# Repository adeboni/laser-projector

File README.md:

# Room-scale Quad Laser Projecter

This project is for a quadruple laser projection controller, aimed at supporting room-scale projections

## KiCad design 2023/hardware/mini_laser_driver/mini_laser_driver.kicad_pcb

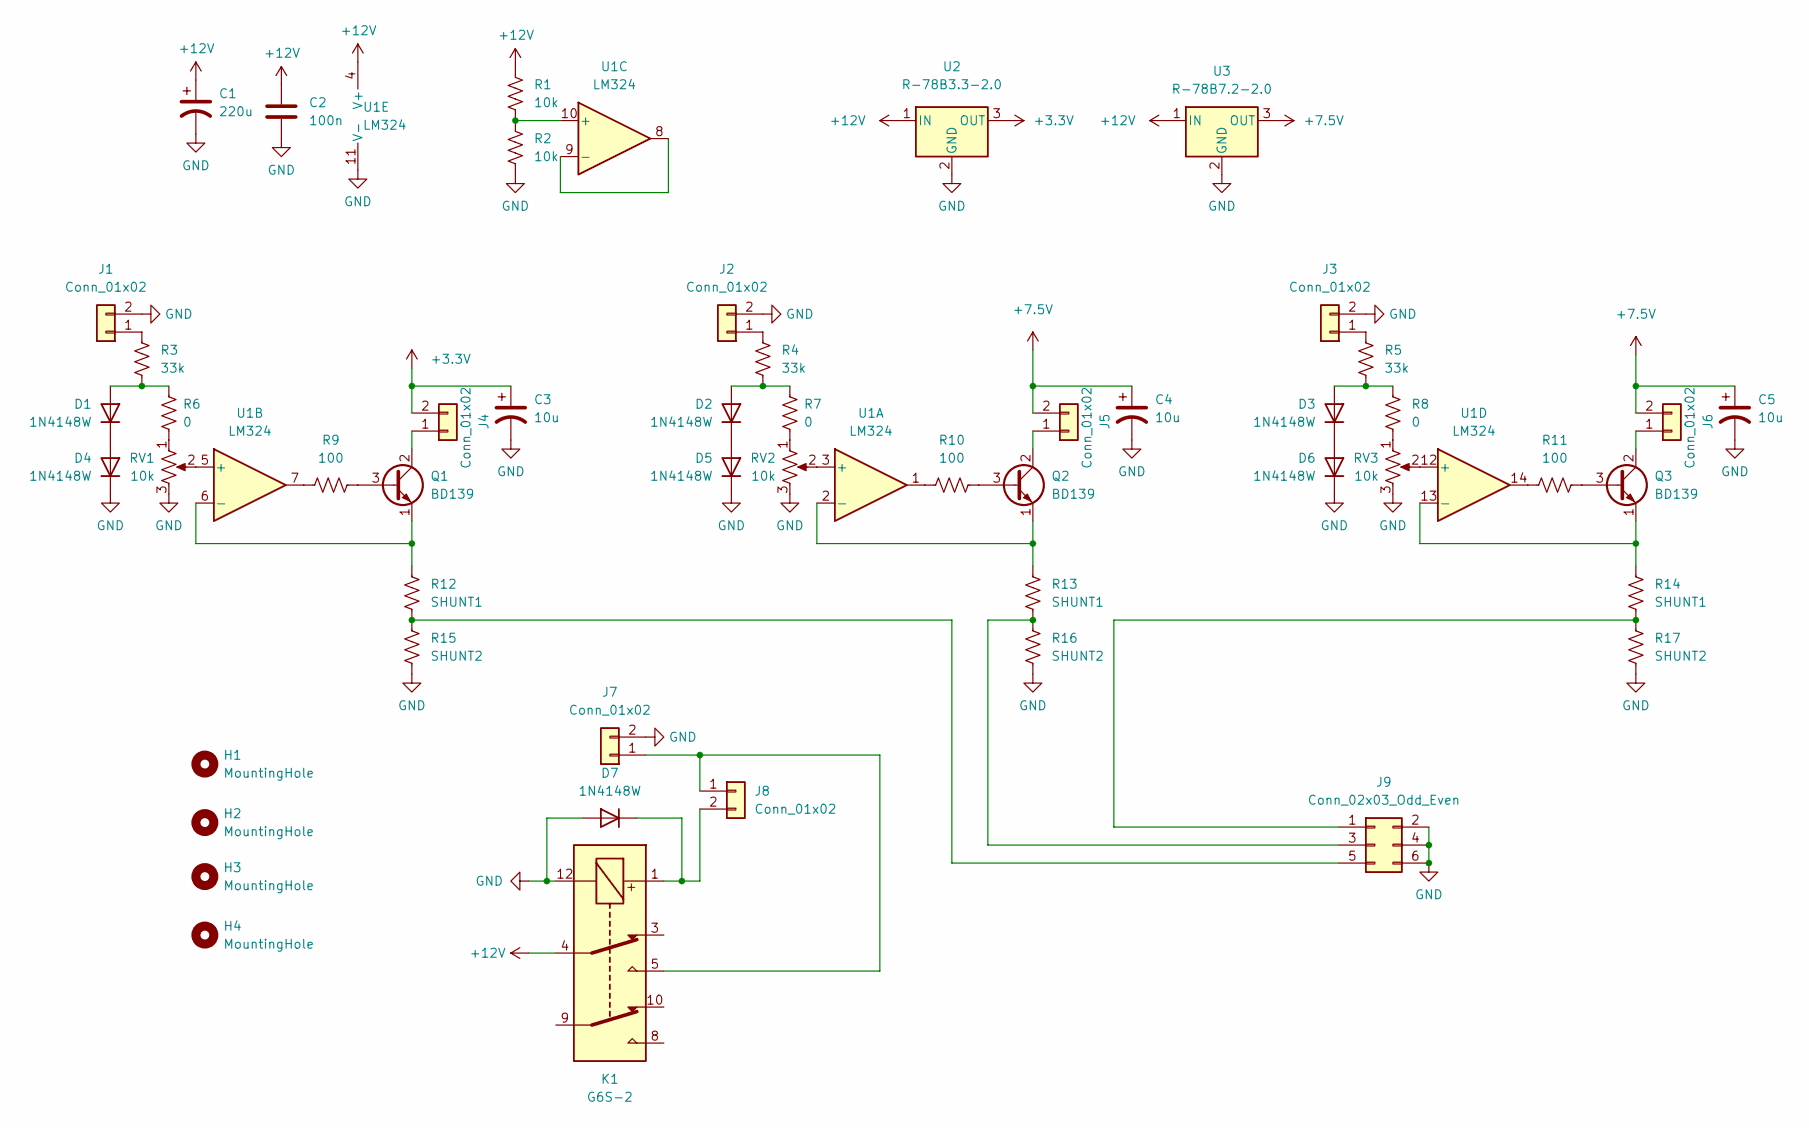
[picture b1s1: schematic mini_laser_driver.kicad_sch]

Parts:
C1: 220u; CP_Radial_D10.0mm_P5.00mm
C2: 100n; C_0603_1608Metric
C3, C4, C5: 10u; CP_Radial_D5.0mm_P2.50mm
D1, D2, D3, D4, D5, D6, D7: 1N4148W; D_SOD-123
H1, H2, H3, H4: MountingHole; MountingHole_3.2mm_M3
J1, J2, J3, J4, J5, J6, J7: Conn_01x02; JST_XH_B2B-XH-A_1x02_P2.50mm_Vertical
J8: Conn_01x02; PinHeader_1x02_P2.54mm_Vertical
J9: Conn_02x03_Odd_Even; PinHeader_2x03_P2.54mm_Vertical
K1: G6S-2; Relay_DPDT_Omron_G6S-2
Q1, Q2, Q3: BD139; TO-126-3_Vertical
R1, R2: 10k; R_0603_1608Metric
R3, R4, R5: 33k; R_0603_1608Metric
R6, R7, R8: 0; R_0603_1608Metric
R9, R10, R11: 100; R_0603_1608Metric
R12, R13, R14: SHUNT1; R_Axial_DIN0204_L3.6mm_D1.6mm_P1.90mm_Vertical
R15, R16, R17: SHUNT2; R_Axial_DIN0204_L3.6mm_D1.6mm_P1.90mm_Vertical
RV1, RV2, RV3: 10k; Potentiometer_Bourns_3296W_Vertical
U1: LM324; SOIC-14_3.9x8.7mm_P1.27mm
U2: R-78B3.3-2.0; Converter_DCDC_RECOM_R-78B-2.0_THT
U3: R-78B7.2-2.0; Converter_DCDC_RECOM_R-78B-2.0_THT

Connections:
+3V3: C3.1, J4.2, U2.3 (OUT)
+7.5V: C4.1, C5.1, J5.2, J6.2, U3.3 (OUT)
+12V: C1.1, C2.1, K1.4, R1.2, U1.4 (V+), U2.1 (IN), U3.1 (IN)
GND: C1.2, C2.2, C3.2, C4.2, C5.2, D4.1 (K), D5.1 (K), D6.1 (K), D7.2 (A), J1.2, J2.2, J3.2, J7.2, J9.2, J9.4, J9.6, K1.12, R2.1, R15.2, R16.2, R17.2, RV1.3, RV2.3, RV3.3, U1.11 (V-), U2.2 (GND), U3.2 (GND)
unnamed: D1.1 (K), D4.2 (A)
unnamed: D1.2 (A), R3.1, R6.2
unnamed: D2.1 (K), D5.2 (A)
unnamed: D2.2 (A), R4.1, R7.2
unnamed: D3.1 (K), D6.2 (A)
unnamed: D3.2 (A), R5.1, R8.2
unnamed: D7.1 (K), J8.2, K1.1
unnamed: J1.1, R3.2
unnamed: J2.1, R4.2
unnamed: J3.1, R5.2
unnamed: J4.1, Q1.2 (C)
unnamed: J5.1, Q2.2 (C)
unnamed: J6.1, Q3.2 (C)
unnamed: J7.1, J8.1, K1.5
unnamed: J9.1, R14.2, R17.1
unnamed: J9.3, R13.2, R16.1
unnamed: Q1.1 (E), R12.1, U1.6 (-)
unnamed: Q1.3 (B), R9.2
unnamed: Q2.1 (E), R13.1, U1.2 (-)
unnamed: Q2.3 (B), R10.2
unnamed: Q3.1 (E), R14.1, U1.13 (-)
unnamed: Q3.3 (B), R11.2
unnamed: R1.1, R2.2, U1.10 (+)
unnamed: R6.1, RV1.1
unnamed: R7.1, RV2.1
unnamed: R8.1, RV3.1
unnamed: R9.1, U1.7
unnamed: R10.1, U1.1
unnamed: R11.1, U1.14
unnamed: J9.5, R12.2, R15.1
unnamed: RV1.2, U1.5 (+)
unnamed: RV2.2, U1.3 (+)
unnamed: RV3.2, U1.12 (+)
unnamed: U1.8, U1.9 (-)

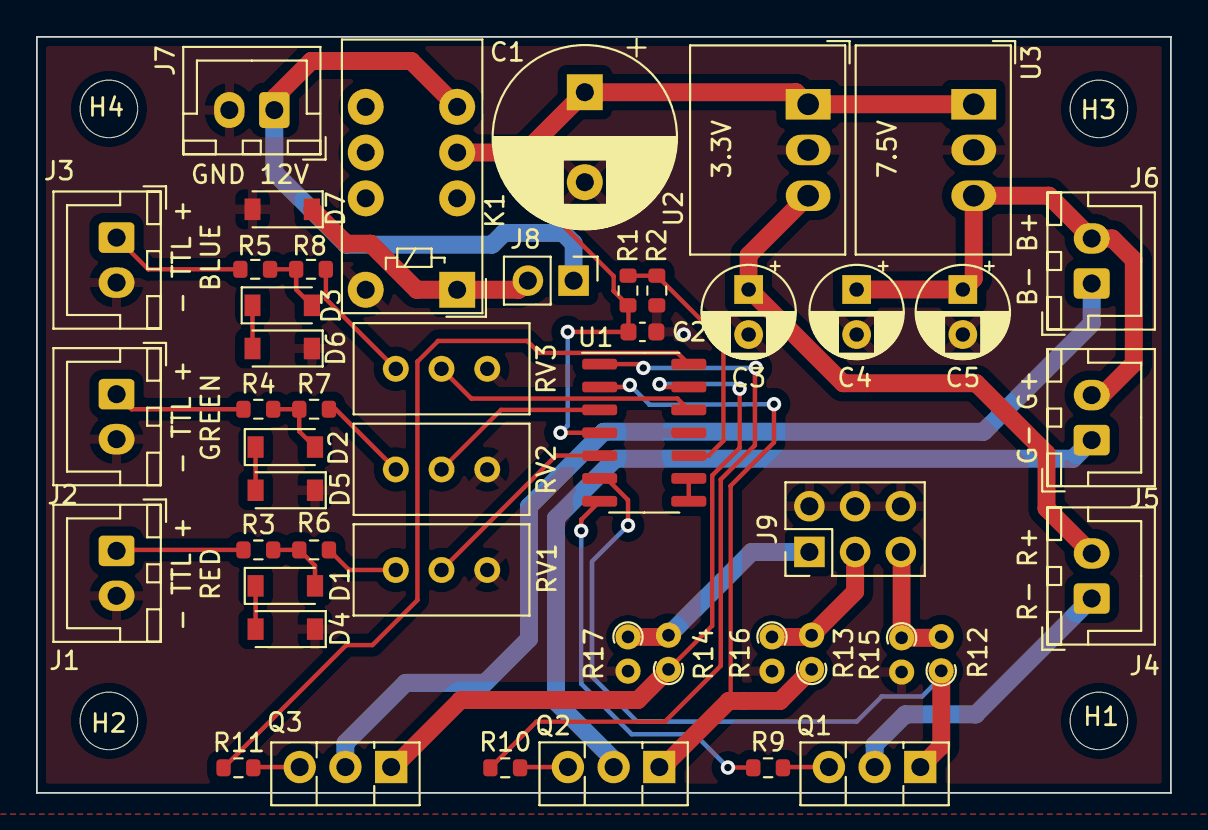
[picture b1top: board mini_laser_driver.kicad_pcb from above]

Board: 2 copper layers, 63.0 x 42.0 mm, 52 parts (0 on the bottom side), 38 nets.

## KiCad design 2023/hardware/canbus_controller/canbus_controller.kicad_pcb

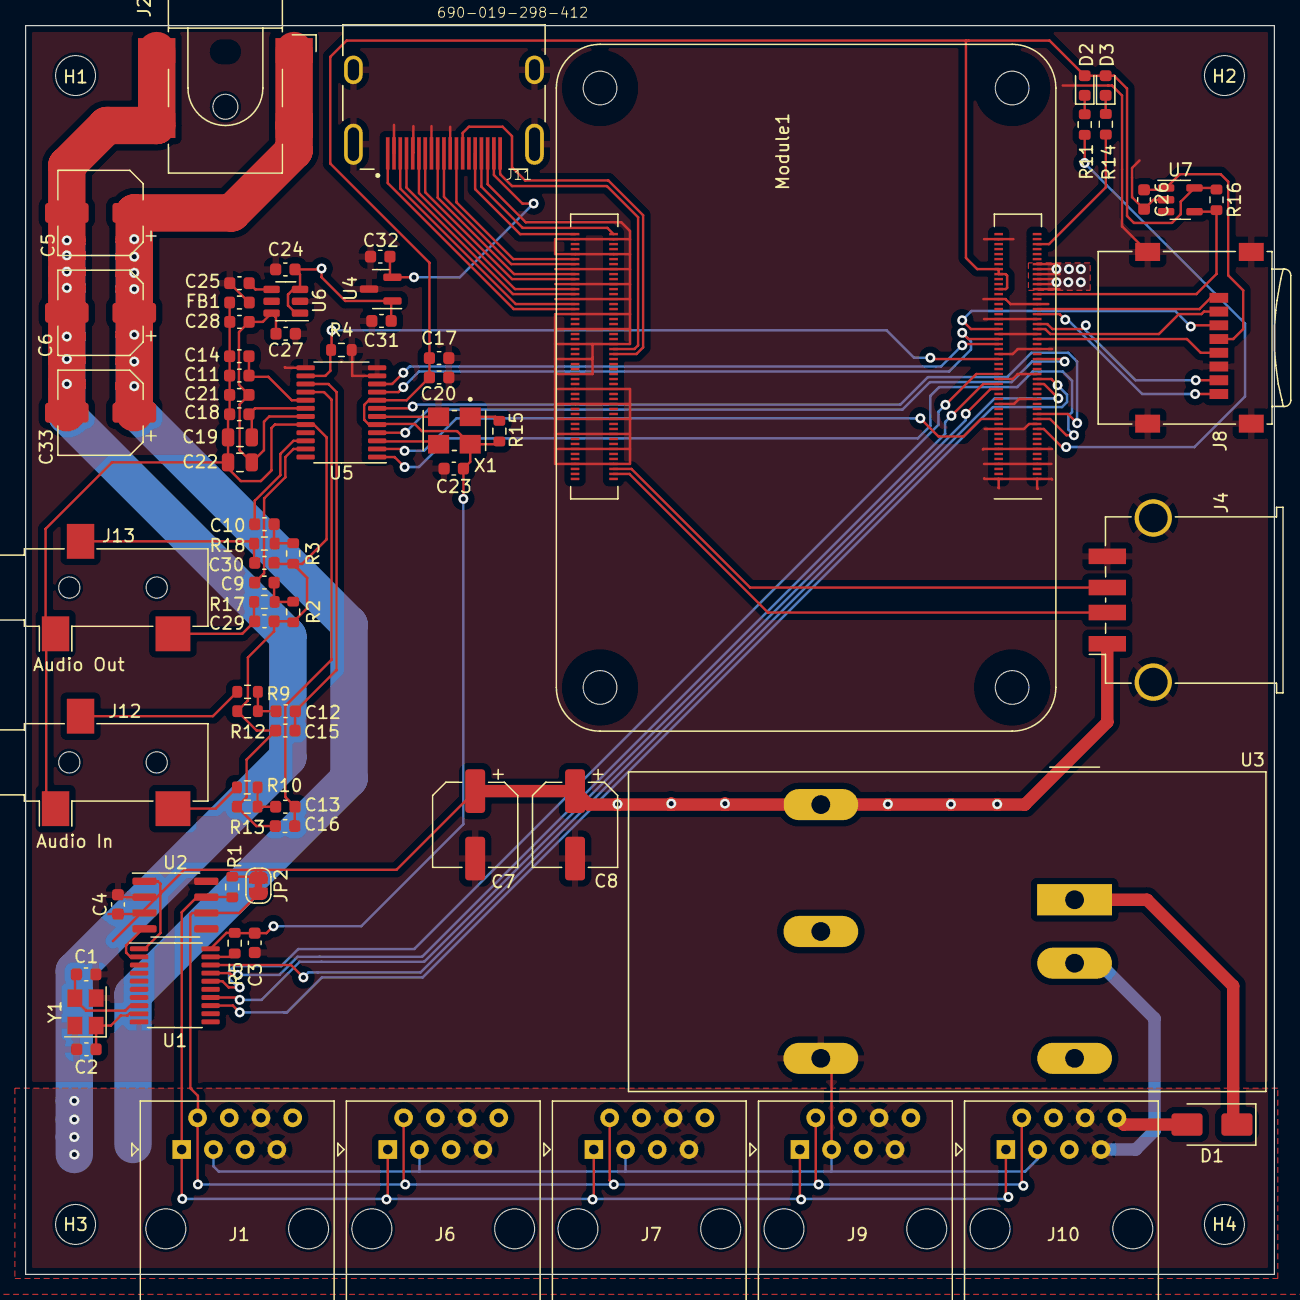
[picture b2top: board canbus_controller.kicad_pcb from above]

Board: 2 copper layers, 100.0 x 100.0 mm, 78 parts (0 on the bottom side), 72 nets.

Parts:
C1, C2: 27p; C_0603_1608Metric
C3, C4, C11, C18, C20, C21, C24, C28, C31, C32: 100n; C_0603_1608Metric
C5, C6, C7, C8, C33: 100u; CP_Elec_6.3x5.8
C9, C10: 3.3u; C_0603_1608Metric
C12, C13, C14, C17, C26, C27: 10u; C_0603_1608Metric
C15, C16: 220p; C_0603_1608Metric
C19, C22: 47u; C_0805_2012Metric
C23, C25: 10n; C_0603_1608Metric
C29, C30: 2.7n; C_0603_1608Metric
D1: SS54; D_SMA
D2: LED Green; LED_0603_1608Metric
D3: LED Red; LED_0603_1608Metric
FB1: FerriteBead_Small; L_0603_1608Metric
H1, H2, H3, H4: MountingHole; MountingHole_3.2mm_M3
J1, J6, J7, J9, J10: RJ45; RJ45_Amphenol_54602-x08_Horizontal
J2: Barrel_Jack_Switch; BarrelJack_CLIFF_FC681465S_SMT_Horizontal
J4: USB_A; USB_A_TE_292303-7_Horizontal
J8: Micro_SD_Card; microSD_HC_Wuerth_693072010801
J11: 690-019-298-412; EDAC 690-019-298-412
J12, J13: AudioJack3; Jack_3.5mm_CUI_SJ-3523-SMT_Horizontal
JP2: SolderJumper_2_Bridged; SolderJumper-2_P1.3mm_Bridged_RoundedPad1.0x1.5mm
Module1: ComputeModule4; Raspberry-Pi-4-Compute-Module
R1: 120; R_0603_1608Metric
R2, R3, R4, R5, R12, R13, R15: 10k; R_0603_1608Metric
R9, R10: 4.99k; R_0603_1608Metric
R11, R14: 1k; R_0603_1608Metric
R16: 12K 1%; R_0603_1608Metric
R17, R18: 590; R_0603_1608Metric
U1: MCP2515-xST; TSSOP-20_4.4x6.5mm_P0.65mm
U2: MCP2551-I-SN; SOIC-8_3.9x4.9mm_P1.27mm
U3: TEN20-2411WIN; Converter_DCDC_TRACO_TEN20-xxxx_THT
U4: RT9742SNGV; SOT-23
U5: CS4270; TSSOP-24_4.4x7.8mm_P0.65mm
U6: TPS79301-EP; SOT-23-6
U7: RT9742GGJ5; SOT-23-5
X1: 12.288MHz; XTAL_ASFL1-8.000MHZ-EC-T
Y1: 8Mhz; Crystal_SMD_3225-4Pin_3.2x2.5mm

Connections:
+5VA: C21.1, C22.1, C27.1, C28.1, U5.19 (VA), U6.6 (OUT)
/+3.3v: C3.1, C17.1, C20.1, C23.1, D2.2 (A), D3.2 (A), Module1.78 (GPIO_VREF(1.8v/3.3v_Input)), Module1.84 (+3.3v_(Output)), Module1.86 (+3.3v_(Output)), R5.2, R15.1, R16.1, U1.20 (VDD), U5.5 (VD), U5.8 (VLC), U7.5 (IN), X1.4 (Vdd)
/+5v: C4.1, C7.1, C8.1, C24.1, C31.1, J4.1 (VBUS), Module1.77 (+5v_(Input)), Module1.79 (+5v_(Input)), Module1.81 (+5v_(Input)), Module1.83 (+5v_(Input)), Module1.85 (+5v_(Input)), Module1.87 (+5v_(Input)), U2.3 (VDD), U3.3 (VOUT+), U4.1 (IN), U6.1 (IN), U6.3 (EN)
/+12v: C5.1, C6.1, C33.1, D1.2 (A), J1.5, J1.8, J2.1, J6.5, J6.8, J7.5, J7.8, J9.5, J9.8, J10.5, J10.8
/HDMI0_CEC: J11.13 (CEC), Module1.151 (HDMI0_CEC)
/HDMI0_CK_N: J11.12 (CK-), Module1.190 (HDMI0_CLK_N)
/HDMI0_CK_P: J11.10 (CK+), Module1.188 (HDMI0_CLK_P)
/HDMI0_D0_N: J11.9 (D0-), Module1.184 (HDMI0_TX0_N)
/HDMI0_D0_P: J11.7 (D0+), Module1.182 (HDMI0_TX0_P)
/HDMI0_D1_N: J11.6 (D1-), Module1.178 (HDMI0_TX1_N)
/HDMI0_D1_P: J11.4 (D1+), Module1.176 (HDMI0_TX1_P)
/HDMI0_D2_N: J11.3 (D2-), Module1.172 (HDMI0_TX2_N)
/HDMI0_D2_P: J11.1 (D2+), Module1.170 (HDMI0_TX2_P)
/HDMI0_HOTPLUG: J11.19 (HPD/HEAC-), Module1.153 (HDMI0_HOTPLUG)
/HDMI0_SCL: J11.15 (SCL), Module1.200 (HDMI0_SCL)
/HDMI0_SDA: J11.16 (SDA), Module1.199 (HDMI0_SDA)
/HDMI_5v: C32.1, J11.18 (+5V), U4.2 (OUT)
/SD_CLK: J8.5 (CLK), Module1.57 (SD_CLK)
/SD_CMD: J8.3 (CMD), Module1.62 (SD_CMD)
/SD_DAT0: J8.7 (DAT0), Module1.63 (SD_DAT0)
/SD_DAT1: J8.8 (DAT1), Module1.67 (SD_DAT1)
/SD_DAT2: J8.1 (DAT2), Module1.69 (SD_DAT2)
/SD_DAT3: J8.2 (DAT3/CD), Module1.61 (SD_DAT3)
/SD_PWR: C26.1, J8.4 (VDD), U7.1 (OUT)
/SD_PWR_ON: Module1.75 (SD_PWR_ON), R16.2, U7.4 (EN)
/USBD_N: J4.2 (D-), Module1.103 (USB2_N)
/USBD_P: J4.3 (D+), Module1.105 (USB2_P)
/nPWR_LED: Module1.95 (nPI_LED_PWR), R14.2
CAN_CS: Module1.39 (GPIO8), U1.18 (~CS)
CAN_H: J1.1, J6.1, J7.1, J9.1, J10.1, R1.2, U2.7 (CANH)
CAN_L: J1.2, J6.2, J7.2, J9.2, J10.2, JP2.2 (B), U2.6 (CANL)
CAN_SCK: Module1.38 (GPIO11), U1.14 (SCK)
CAN_SI: Module1.44 (GPIO10), U1.16 (SI)
CAN_SO: Module1.40 (GPIO9), U1.17 (SO)
GND: C1.2, C2.2, C3.2, C4.2, C7.2, C8.2, C17.2, C20.2, C23.2, C24.2, C25.2, C26.2, C27.2, C31.2, C32.2, FB1.2, J1.3, J4.4 (GND), J4.5 (Shield), J6.3, J7.3, J8.6 (VSS), J8.9 (SHIELD), J9.3, J10.3, J11.2 (D2S), J11.5 (D1S), J11.8 (D0S), J11.11 (CKS), J11.17 (GND), J11.SH1 (SH), J11.SH2 (SH), J11.SH3 (SH), J11.SH4 (SH), Module1.1 (GND), Module1.2 (GND), Module1.7 (GND), Module1.8 (GND), Module1.13 (GND), Module1.14 (GND), Module1.22 (GND), Module1.23 (GND), Module1.32 (GND), Module1.33 (GND), Module1.42 (GND), Module1.43 (GND), Module1.52 (GND), Module1.53 (GND), Module1.59 (GND), Module1.60 (GND), Module1.65 (GND), Module1.66 (GND), Module1.71 (GND), Module1.74 (GND), Module1.98 (GND), Module1.107 (GND), Module1.108 (GND), Module1.113 (GND), Module1.114 (GND), Module1.119 (GND), Module1.120 (GND), Module1.125 (GND), Module1.126 (GND), Module1.131 (GND), Module1.132 (GND), Module1.137 (GND), Module1.138 (GND), Module1.144 (GND), Module1.150 (GND), Module1.155 (GND), Module1.156 (GND), Module1.161 (GND), Module1.162 (GND), Module1.167 (GND), Module1.168 (GND), Module1.173 (GND), Module1.174 (GND), Module1.179 (GND), Module1.180 (GND), Module1.185 (GND), Module1.186 (GND), Module1.191 (GND), Module1.192 (GND), Module1.197 (GND), Module1.198 (GND), R4.1, U1.10 (VSS), U2.2 (VSS), U2.8 (Rs), U3.5 (VOUT-), U4.3 (GND), U5.6 (DGND), U5.11 (AD0/~CS/I2S/~LJ), U5.12 (AD1/CDIN/MDIV1), U5.13 (AD2/MDIV2), U6.2 (GND), U7.2 (GND), X1.2 (GND), Y1.2, Y1.4
GNDA: C11.2, C14.2, C15.1, C16.1, C18.2, C19.2, C21.2, C22.2, C28.2, C29.1, C30.1, FB1.1, J12.S, J13.S, R2.2, R3.2, R12.2, R13.2, U5.20 (AGND)
GNDPWR: C5.2, C6.2, C33.2, J1.6, J1.7, J2.2, J2.3, J6.6, J6.7, J7.6, J7.7, J9.6, J9.7, J10.6, J10.7, U3.2 (VIN-)
GPIO25: Module1.41 (GPIO25), U1.13 (~INT)
INA: C12.2, C15.2, U5.15 (AINA)
INB: C13.2, C16.2, U5.16 (AINB)
LRCLK: Module1.26 (GPIO19), U5.2 (LRCLK)
MCLK: U5.3 (MCLK), X1.3 (OUT)
unnamed: C9.2, R2.1, R17.2
unnamed: C10.2, R3.1, R18.2
unnamed: C12.1, R9.1, R12.1
unnamed: C13.1, R10.1, R13.1
unnamed: C29.2, J13.T, R17.1
unnamed: C30.2, J13.R, R18.1
unnamed: D1.1 (K), U3.1 (VIN+)
unnamed: D2.1 (K), R11.1
unnamed: D3.1 (K), R14.1
unnamed: J12.R, R9.2
unnamed: J12.T, R10.2
unnamed: JP2.1 (A), R1.1
unnamed: Module1.21 (PI_nLED_Activity), R11.2
unnamed: C2.1, U1.9 (OSC1), Y1.1
unnamed: C1.1, U1.8 (OSC2), Y1.3
unnamed: U1.2 (RXCAN), U2.4 (RXD)
unnamed: U1.1 (TXCAN), U2.1 (TXD)
unnamed: R5.1, U1.19 (~RESET)
unnamed: C18.1, C19.1, U5.18 (FIL+)
unnamed: C11.1, C14.1, U5.17 (VQ)
unnamed: C25.1, U6.4 (BP)
unnamed: R15.2, X1.1 (EN)
OUTA: C10.1, U5.22 (OUTA)
OUTB: C9.1, U5.23 (OUTB)
R_CODEC: Module1.50 (GPIO17), R4.2, U5.14 (~RST)
SCLK: Module1.49 (GPIO18), U5.4 (SCLK)
SCL_CODEC: Module1.56 (GPIO3), U5.10 (SCL/CCLK/M0)
SDA_CODEC: Module1.58 (GPIO2), U5.9 (SDA/CDOUT/M1)
SDIN: Module1.25 (GPIO21), U5.1 (SDIN)
SDOUT: Module1.27 (GPIO20), U5.7 (SDOUT)

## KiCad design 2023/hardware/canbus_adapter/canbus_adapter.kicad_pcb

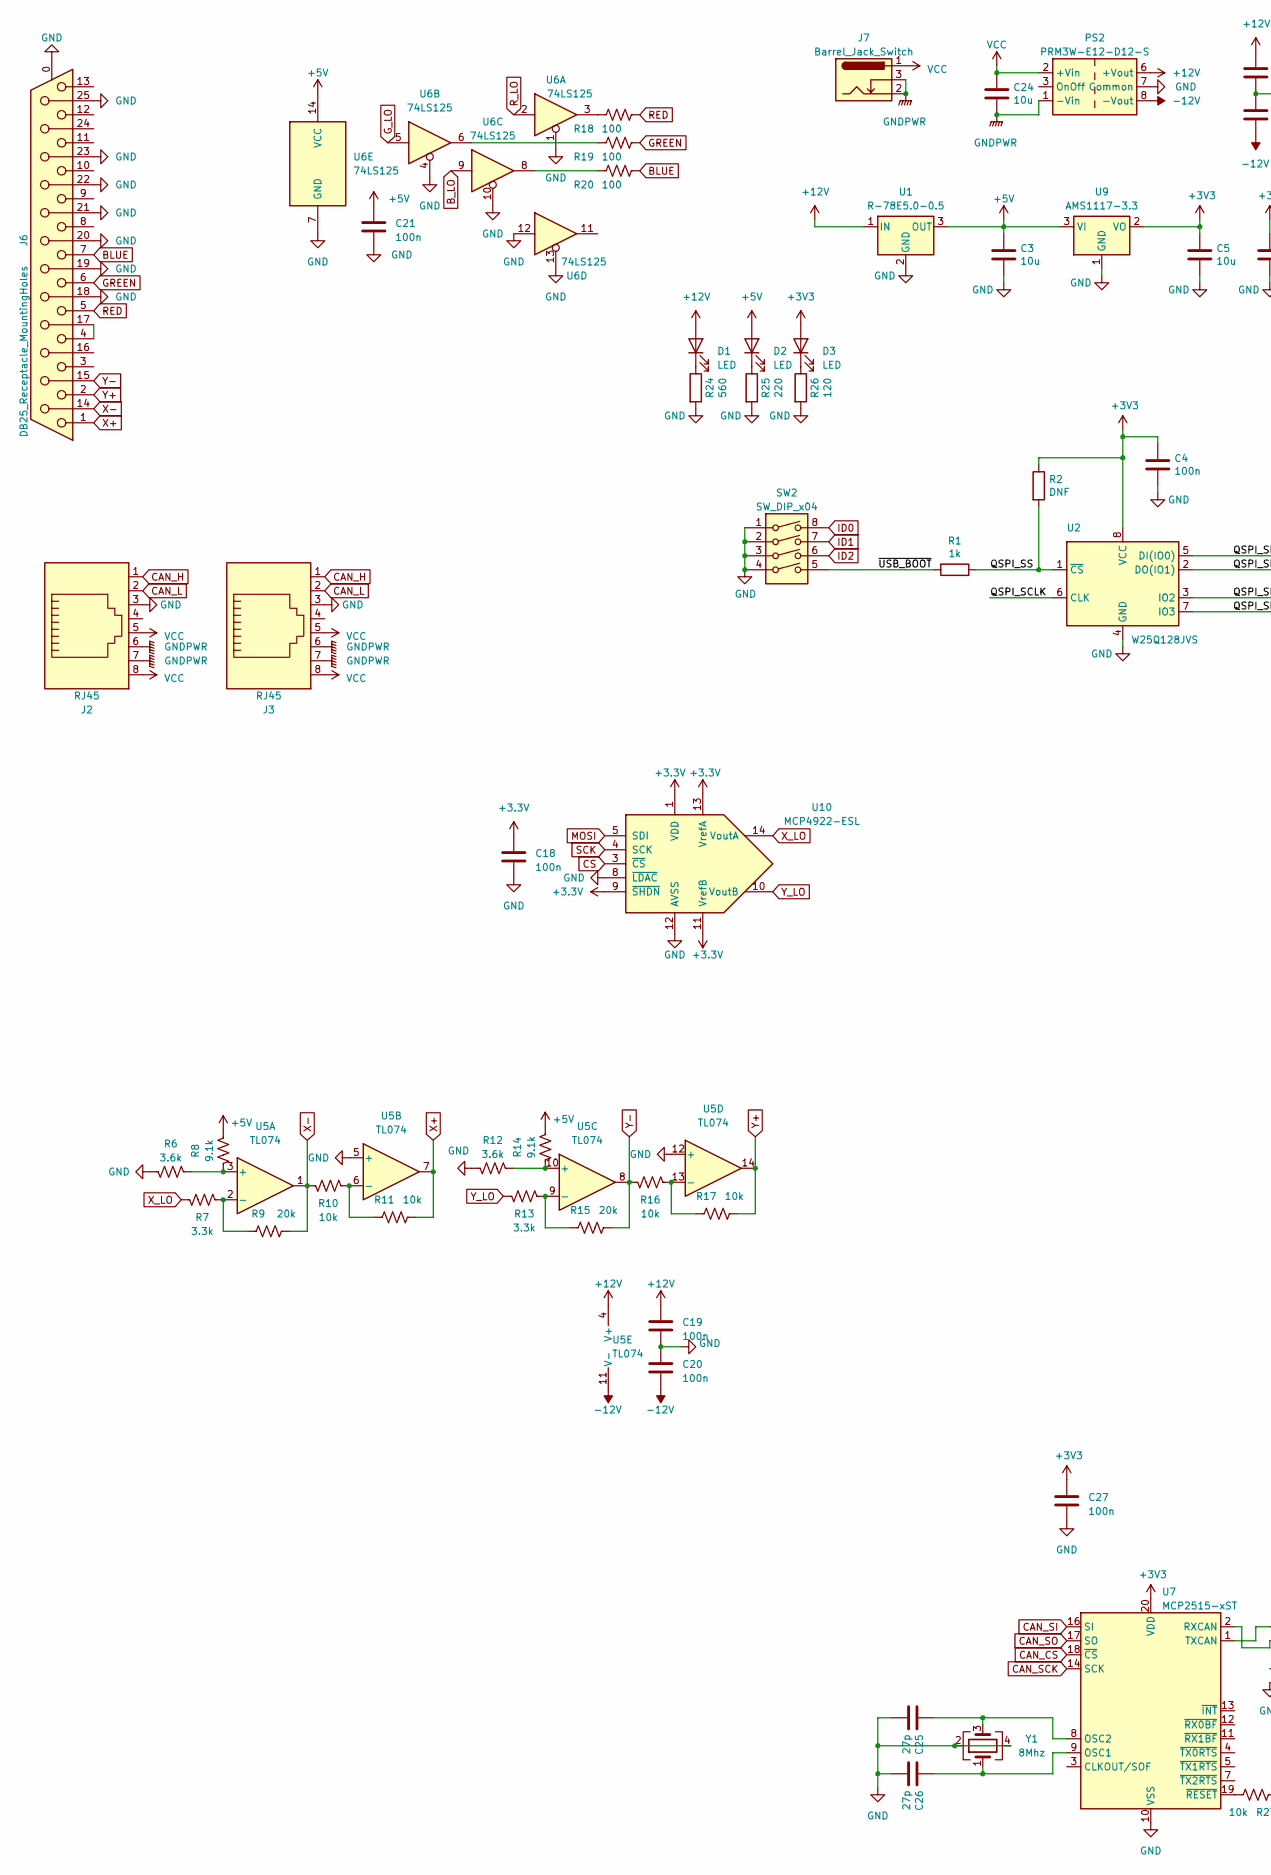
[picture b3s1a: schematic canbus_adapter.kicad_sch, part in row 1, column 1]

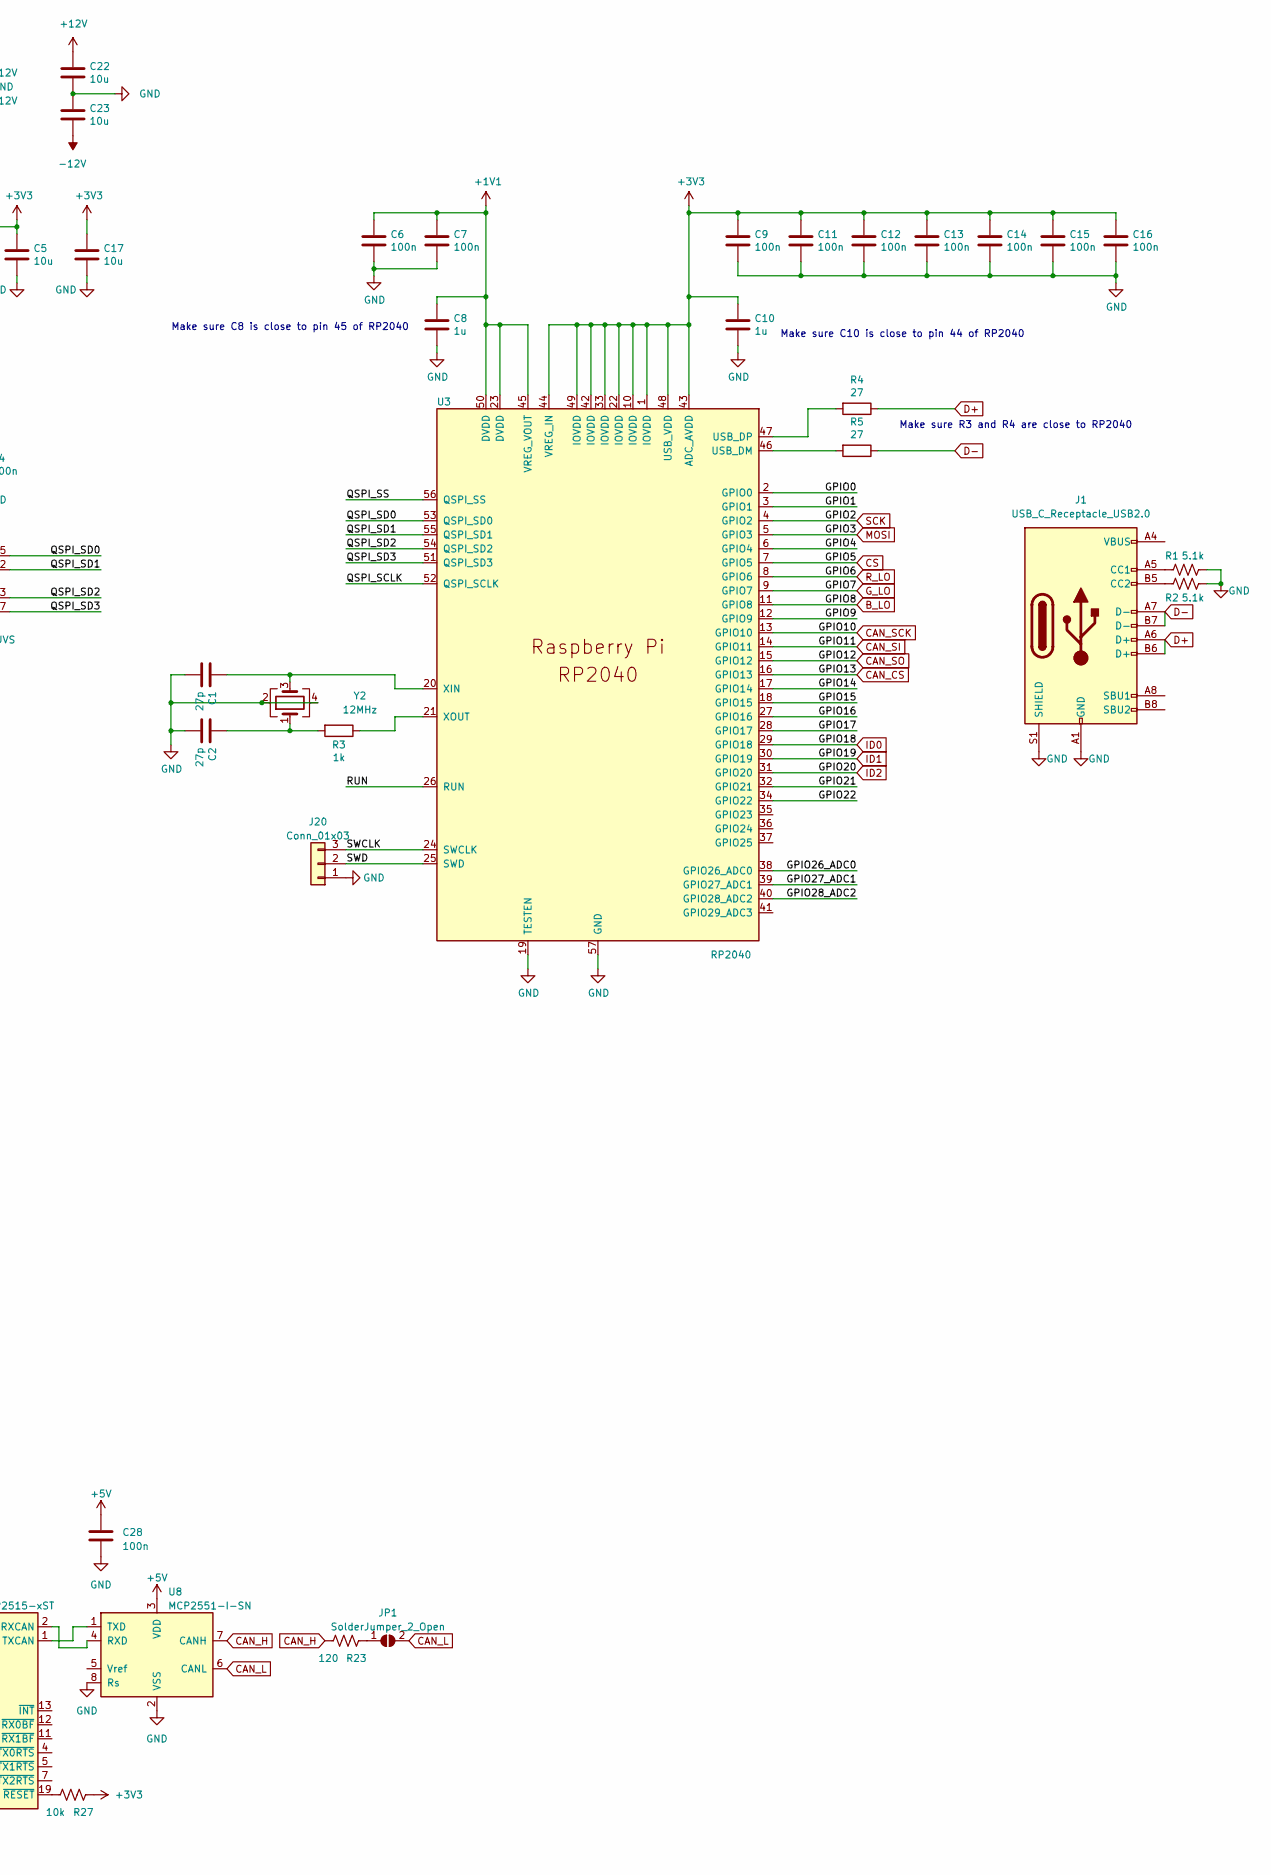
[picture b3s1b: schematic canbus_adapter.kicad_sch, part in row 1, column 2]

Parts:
C1, C2, C25, C26: 27p; C_0603_1608Metric
C3, C5, C17, C22, C23, C24: 10u; C_0603_1608Metric
C4, C6, C7, C9, C11, C12, C13, C14, C15, C16, C18, C19, C20, C21, C27, C28: 100n; C_0603_1608Metric
C8, C10: 1u; C_0603_1608Metric
D1, D2, D3: LED; LED_0603_1608Metric
J1: USB_C_Receptacle_USB2.0; USB_C_Receptacle_Palconn_UTC16-G
J2, J3: RJ45; RJ45_Amphenol_54602-x08_Horizontal
J6: DB25_Receptacle_MountingHoles; DSUB-25_Female_Horizontal_P2.77x2.84mm_EdgePinOffset7.70mm_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
J7: Barrel_Jack_Switch; BarrelJack_CLIFF_FC681465S_SMT_Horizontal
J20: Conn_01x03; PinHeader_1x03_P2.54mm_Vertical
JP1: SolderJumper_2_Open; SolderJumper-2_P1.3mm_Open_RoundedPad1.0x1.5mm
PS2: PRM3W-E12-D12-S; Converter_DCDC_XP_POWER-ITxxxxxS_THT
R1: 5.1k; R_0603_1608Metric
R2: DNF; R_0603_1608Metric
R3: 1k; R_0603_1608Metric
R4, R5: 27; R_0603_1608Metric
R6, R12: 3.6k; R_0603_1608Metric
R7, R13: 3.3k; R_0603_1608Metric
R8, R14: 9.1k; R_0603_1608Metric
R9, R15: 20k; R_0603_1608Metric
R10, R11, R16, R17, R27: 10k; R_0603_1608Metric
R18, R19, R20: 100; R_0603_1608Metric
R23, R26: 120; R_0603_1608Metric
R24: 560; R_0603_1608Metric
R25: 220; R_0603_1608Metric
SW2: SW_DIP_x04; SW_DIP_SPSTx04_Slide_Omron_A6S-410x_W8.9mm_P2.54mm
U1: R-78E5.0-0.5; Converter_DCDC_RECOM_R-78E-0.5_THT
U2: W25Q128JVS; SOIC-8_5.23x5.23mm_P1.27mm
U3: RP2040; QFN-56-1EP_7x7mm_P0.4mm_EP3.2x3.2mm
U5: TL074; SOIC-14_3.9x8.7mm_P1.27mm
U6: 74LS125; SOIC-14_3.9x8.7mm_P1.27mm
U7: MCP2515-xST; TSSOP-20_4.4x6.5mm_P0.65mm
U8: MCP2551-I-SN; SOIC-8_3.9x4.9mm_P1.27mm
U9: AMS1117-3.3; SOT-223-3_TabPin2
U10: MCP4922-ESL; SOIC-14_3.9x8.7mm_P1.27mm
Y1: 8Mhz; Crystal_SMD_3225-4Pin_3.2x2.5mm
Y2: 12MHz; Crystal_SMD_3225-4Pin_3.2x2.5mm

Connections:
+1V1: C6.1, C7.1, C8.1, U3.23 (DVDD), U3.45 (VREG_VOUT), U3.50 (DVDD)
+5V: C3.1, C21.1, C28.1, D2.2 (A), R8.2, R14.2, U1.3 (OUT), U6.14 (VCC), U8.3 (VDD), U9.3 (VI)
+12V: C19.1, C22.1, D1.2 (A), PS2.6 (+Vout), U1.1 (IN), U5.4 (V+)
-12V: C20.2, C23.2, PS2.8 (-Vout), U5.11 (V-)
/GPIO0: U3.2 (GPIO0)
/GPIO1: U3.3 (GPIO1)
/GPIO4: U3.6 (GPIO4)
/GPIO9: U3.12 (GPIO9)
/GPIO14: U3.17 (GPIO14)
/GPIO15: U3.18 (GPIO15)
/GPIO16: U3.27 (GPIO16)
/GPIO17: U3.28 (GPIO17)
/GPIO21: U3.32 (GPIO21)
/GPIO22: U3.34 (GPIO22)
/GPIO26_ADC0: U3.38 (GPIO26_ADC0)
/GPIO27_ADC1: U3.39 (GPIO27_ADC1)
/GPIO28_ADC2: U3.40 (GPIO28_ADC2)
/QSPI_SCLK: U2.6 (CLK), U3.52 (QSPI_SCLK)
/QSPI_SD0: U2.5 (DI(IO0)), U3.53 (QSPI_SD0)
/QSPI_SD1: U2.2 (DO(IO1)), U3.55 (QSPI_SD1)
/QSPI_SD2: U2.3 (IO2), U3.54 (QSPI_SD2)
/QSPI_SD3: U2.7 (IO3), U3.51 (QSPI_SD3)
/RUN: U3.26 (RUN)
/SWCLK: U3.24 (SWCLK); also elsewhere on the board
/SWD: U3.25 (SWD); also elsewhere on the board
BLUE: J6.7, R20.2
B_LO: U3.11 (GPIO8), U6.9
CAN_CS: U3.16 (GPIO13), U7.18 (~CS)
CAN_H: J2.1, J3.1, R23.2, U8.7 (CANH)
CAN_L: J2.2, J3.2, JP1.2 (B), U8.6 (CANL)
CAN_SCK: U3.13 (GPIO10), U7.14 (SCK)
CAN_SI: U3.14 (GPIO11), U7.16 (SI)
CAN_SO: U3.15 (GPIO12), U7.17 (SO)
CS: U3.7 (GPIO5), U10.3 (~CS)
D+: J1.A6 (D+), J1.B6 (D+), R4.1
D-: J1.A7 (D-), J1.B7 (D-), R5.1
GNDPWR: C24.2, J2.6, J2.7, J3.6, J3.7, J7.2, J7.3, PS2.1 (-Vin)
GREEN: J6.6, R19.2
G_LO: U3.9 (GPIO7), U6.5
ID0: SW2.8, U3.29 (GPIO18)
ID1: SW2.7, U3.30 (GPIO19)
ID2: SW2.6, U3.31 (GPIO20)
MOSI: U3.5 (GPIO3), U10.5 (SDI)
unnamed: C2.1, R3.2, Y2.1
unnamed: D1.1 (K), R24.1
unnamed: D2.1 (K), R25.1
unnamed: D3.1 (K), R26.1
unnamed: J1.A4 (VBUS), J1.A9 (VBUS), J1.B4 (VBUS), J1.B9 (VBUS)
unnamed: J6.4, J6.17
unnamed: JP1.1 (A), R23.1
unnamed: R18.1, U6.3
unnamed: R19.1, U6.6
unnamed: R20.1, U6.8
unnamed: R5.2, U3.46 (USB_DM)
unnamed: R4.2, U3.47 (USB_DP)
unnamed: C1.1, U3.20 (XIN), Y2.3
unnamed: R3.1, U3.21 (XOUT)
unnamed: R6.2, R8.1, U5.3 (+)
unnamed: R7.2, R9.1, U5.2 (-)
unnamed: R10.2, R11.1, U5.6 (-)
unnamed: R12.2, R14.1, U5.10 (+)
unnamed: R13.2, R15.1, U5.9 (-)
unnamed: R16.2, R17.1, U5.13 (-)
unnamed: C26.1, U7.9 (OSC1), Y1.1
unnamed: C25.1, U7.8 (OSC2), Y1.3
unnamed: U7.2 (RXCAN), U8.4 (RXD)
unnamed: U7.1 (TXCAN), U8.1 (TXD)
unnamed: R27.2, U7.19 (~RESET)
RED: J6.5, R18.2
R_LO: U3.8 (GPIO6), U6.2
SCK: U3.4 (GPIO2), U10.4 (SCK)
VCC: C24.1, J2.5, J2.8, J3.5, J3.8, J7.1, PS2.2 (+Vin)
X+: J6.1, R11.2, U5.7
X-: J6.14, R9.2, R10.1, U5.1
X_LO: R7.1, U10.14 (VoutA)
Y+: J6.2, R17.2, U5.14
Y-: J6.15, R15.2, R16.1, U5.8
Y_LO: R13.1, U10.10 (VoutB)

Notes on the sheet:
Make sure C8 is close to pin 45 of RP2040
Make sure R3 and R4 are close to RP2040
Make sure C10 is close to pin 44 of RP2040

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
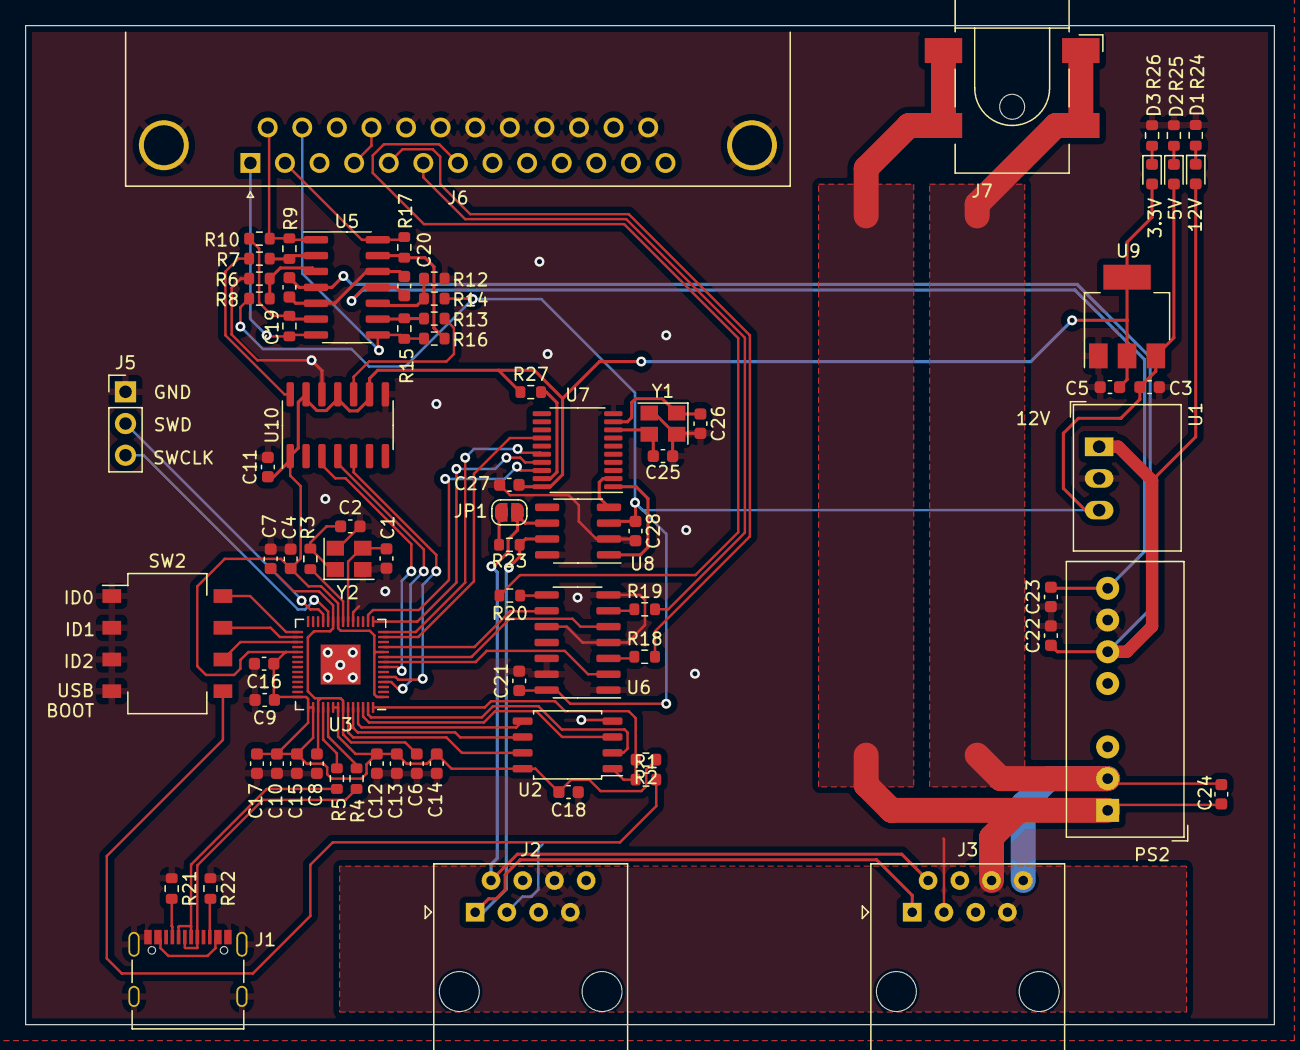
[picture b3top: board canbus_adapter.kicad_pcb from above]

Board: 2 copper layers, 100.0 x 80.0 mm, 78 parts (0 on the bottom side), 70 nets.

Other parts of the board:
J5: Conn_01x03; PinHeader_1x03_P2.54mm_Vertical
R21, R22: 5.1k; R_0603_1608Metric

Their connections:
/SWCLK: J5.3; also elsewhere on the board
/SWD: J5.2; also elsewhere on the board
